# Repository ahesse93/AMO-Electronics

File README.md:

# AMO-Electronics
Collection of different electronics projects useful for AMO experiments  

The supply voltages of different boards can be daisy-chained together using the Molex connectors.

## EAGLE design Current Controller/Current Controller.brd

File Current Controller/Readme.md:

# Current Controller

Regulates a current < 10 A with a Darlington transistor, measuring the current across a 1 Ohm shunt resistor -> 1V = 1A

Regulates the current on the low side, so connect the load on the current input and the output (= ground) back to the power supply
  
C3 can be used to limit the control bandwidth, C4 can be increased to make circuit stable if oscillating.

Appears to be stable for inductive loads of up to 1 mH (and maybe higher).

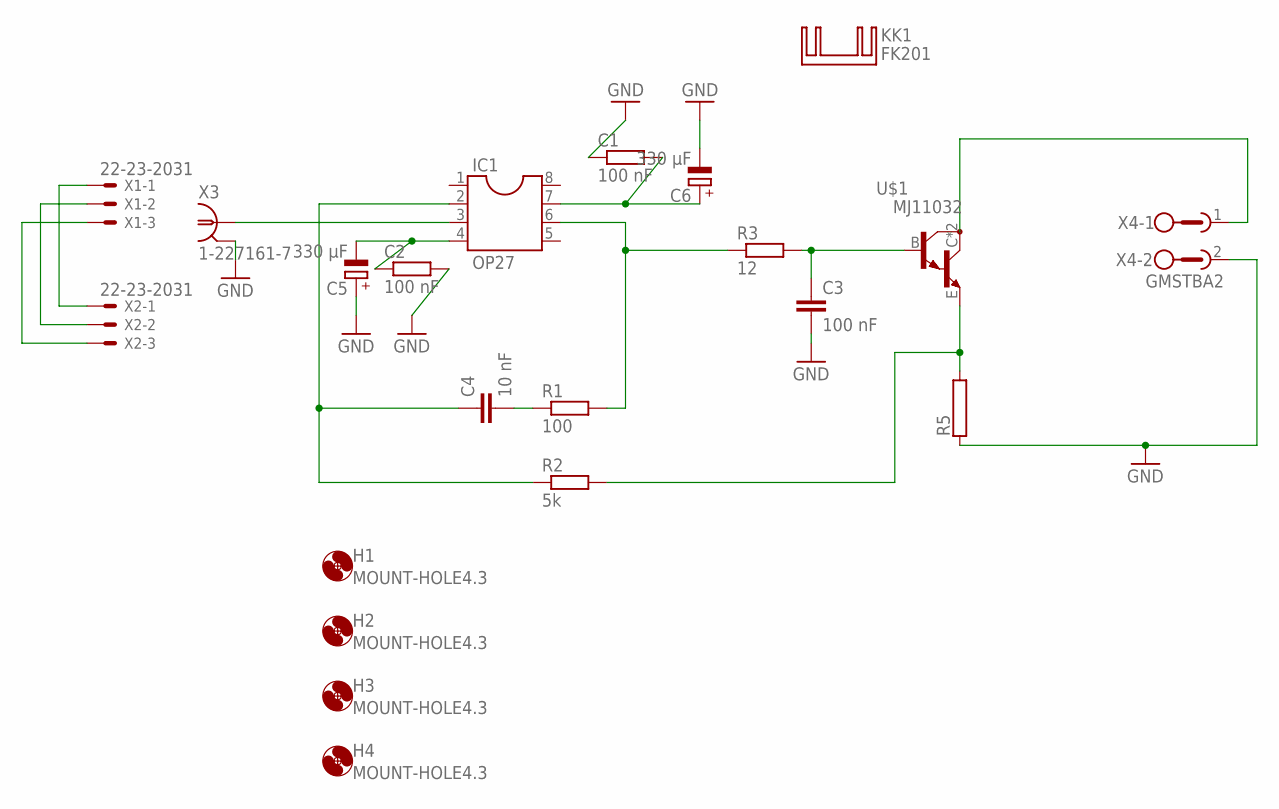
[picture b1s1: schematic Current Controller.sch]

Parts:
C1, C2: 100 nF; M1206
C3: 100 nF; C025-050X050
C4: 10 nF; C025-050X050
C5, C6: 330 µF; E5-8,5
H1, H2, H3, H4: MOUNT-HOLE4.3; 4,3
IC1: OP27; DIL08
KK1: FK201
R1: 100; 0309/12
R2: 5k; 0309/12
R3: 12; 0309/12
R5: RRWM10X64; RWM10X64
U$1: MJ11032; TO3/
X1, X2: 22-23-2031
X3: 1-227161-7; AMP_227161
X4: GMSTBA2

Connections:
-IN: C4.1, IC1.2, R2.1
BASE_VOLTAGE: C3.1, R3.2, U$1.B
CURRENT_IN: U$1.C, U$1.C/ (C), X4.1
GND: C1.1, C2.2, C3.2, C5.+, C6.-, R5.1, X1.2, X2.2, X3.2, X4.2
unnamed: R2.2, R5.2, U$1.E
unnamed: C4.2, R1.1
OPAMP_OUT: IC1.6, R1.2, R3.1
SIG_IN: IC1.3, X3.1
V+: C1.2, C6.+, IC1.7, X1.1, X2.1
V-: C2.1, C5.-, IC1.4, X1.3, X2.3

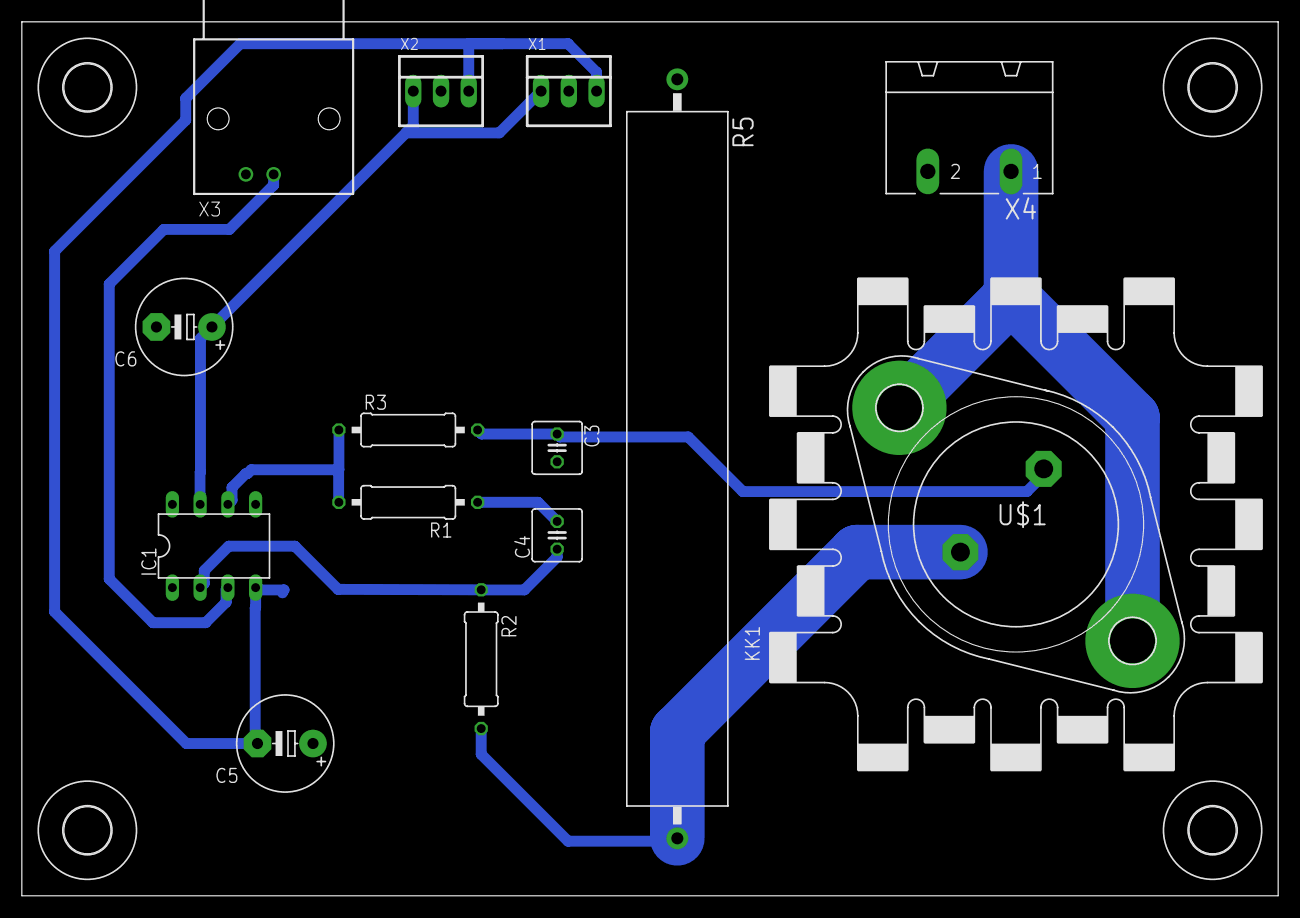
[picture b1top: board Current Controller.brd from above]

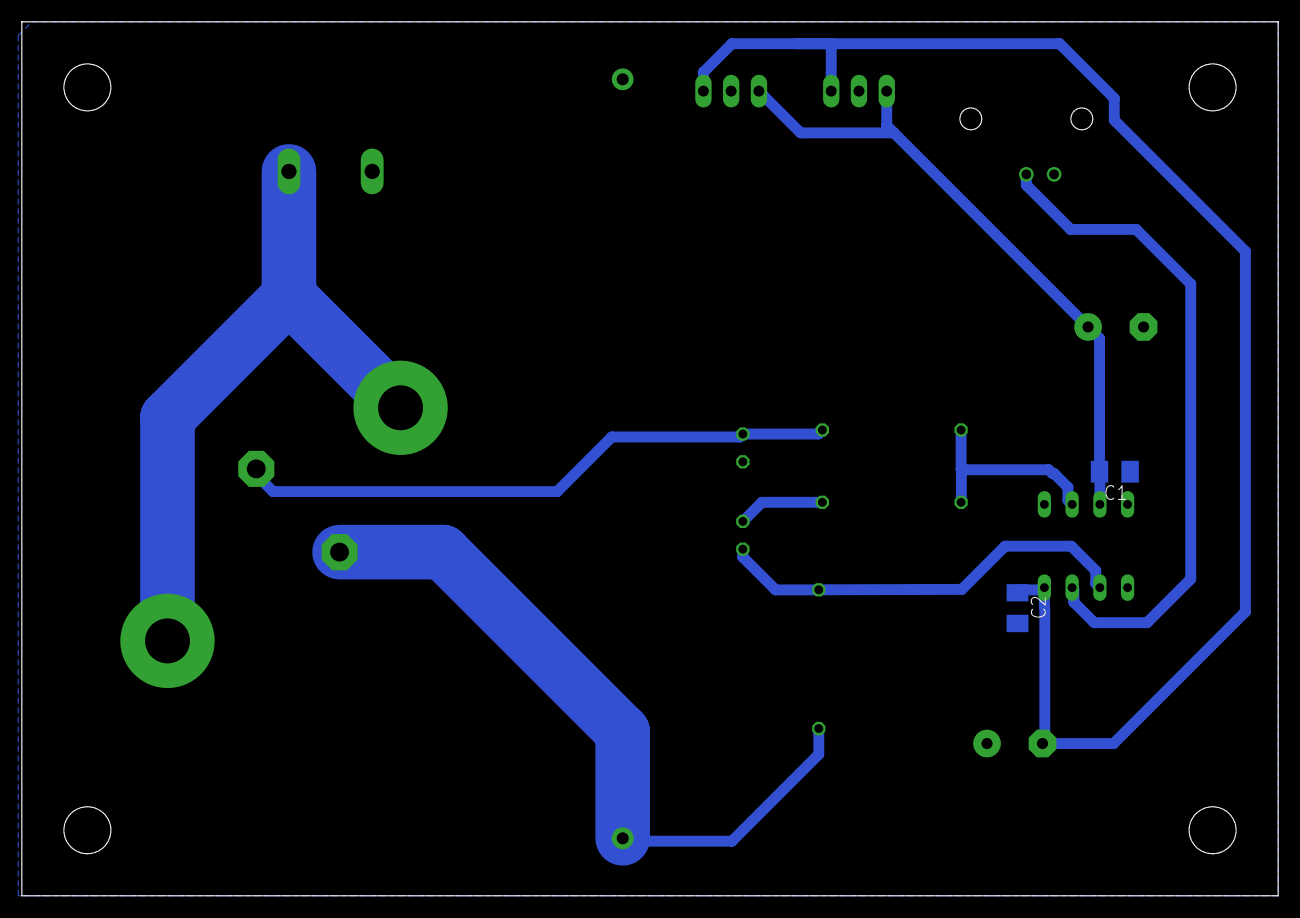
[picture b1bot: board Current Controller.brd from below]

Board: 1 copper layer, 115.0 x 80.0 mm, 21 parts (2 on the bottom side), 10 nets.

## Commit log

2019-02-21 Added space for a heatsink around the Darlington
    Added space for a heatsink around the Darlington
2019-03-29 Add files via upload
    Placed the shunt resistor directly on the board, and did some minor bugfixes
